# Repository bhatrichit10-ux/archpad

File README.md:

# Archpad
A custom-made macropad/hackpad for arch users. <br>Made for blueprint by Hack Club

## PCB (Printed Circuit Board)
The files of PCBs is inside the PCB folder, It contains a KiCad Project, a schematic file and a pcb file. <br>
[PCB file](PCB/richit.kicad_pcb) <br>
[Project File](PCB/richit.kicad_pro) <br>
[Schematic Files](PCB/richit.kicad_sch)
### Images:

## Case (CAD)

### Files: 
[Stp_TOP](production/Archpad_Top_latest.stp) <br>
[Stp_Bottom_Case](production/Archpad_Latest.stp)
## Firmware
The firmware is coded in ~~KMK~~ `adafruit_hid` which is in python.<br>
I have taken help of ChatGPT in this part <br>
[code.py](firmware/HID/code.py)
## Building
It took  me approx 9 hours to physically build this. Here is the final result

## BOM
- Seeed XIAO RP2040 ×1
- MX-style mechanical switches ×6
- Blank DSA keycaps (white) ×6
- 0.91 inch OLED display (SSD1306, I2C) ×1
- SK6812 MINI-E RGB LED ×1
- M3 × 16 mm screws ×4
- M3 heat-set inserts ×4
- 3D printed case ×1
## Thanks HackClub
Special thanks to HackClub and Blueprint for providing this opportunity. 
Join them : [HackClub](https://hackclub.com) <br>
Blueprint : [Blueprint](https://blueprint.hackclub.com)
## Whats next?
I am working on making another cool projects like this

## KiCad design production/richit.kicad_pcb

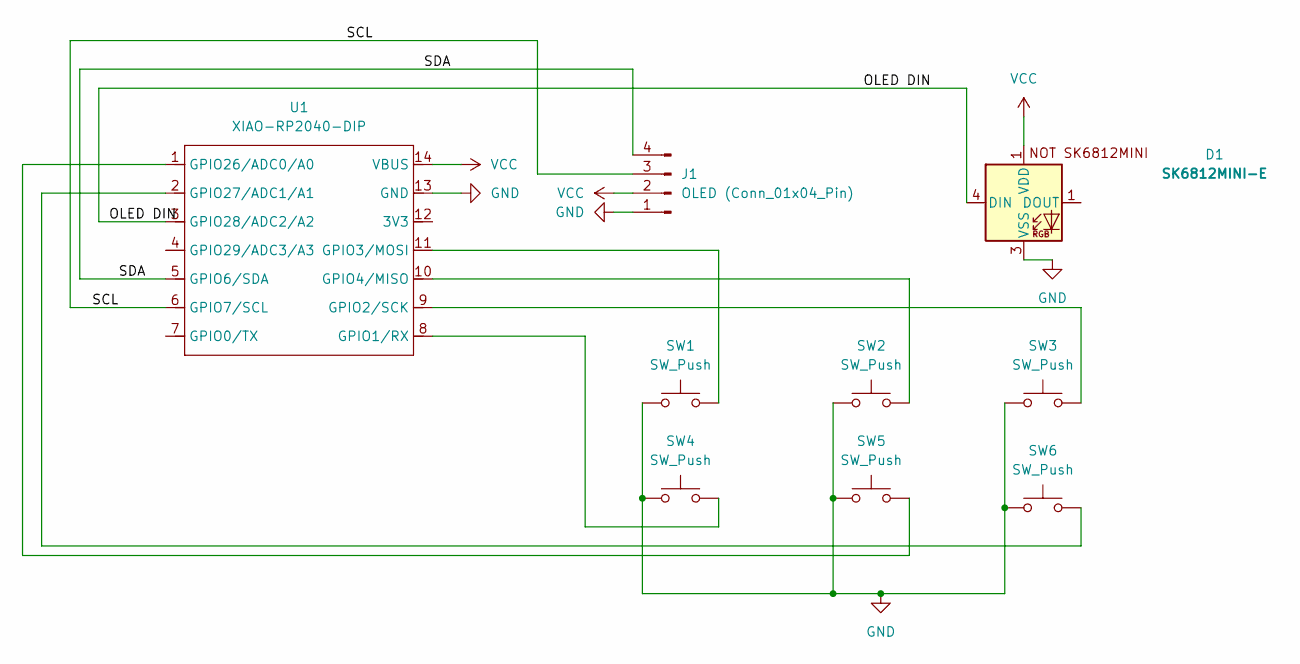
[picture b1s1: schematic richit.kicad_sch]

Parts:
D1: SK6812MINI-E; SK6812MINI-E_fixed
J1: OLED (Conn_01x04_Pin); SSD1306-0.91-OLED-4pin-128x32
SW1, SW2, SW3, SW4, SW5, SW6: SW_Push; SW_Cherry_MX_1.00u_PCB
U1: XIAO-RP2040-DIP; XIAO-Generic-Hybrid-14P-2.54-21X17.8MM

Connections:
/SCL: J1.3, U1.6 (GPIO7/SCL)
/SDA: J1.4, U1.5 (GPIO6/SDA)
GND: D1.3 (VSS), J1.1, SW1.1, SW2.1, SW3.1, SW4.1, SW5.1, SW6.1, U1.13 (GND)
unnamed: D1.4 (DIN), U1.3 (GPIO28/ADC2/A2)
unnamed: SW4.2, U1.8 (GPIO1/RX)
unnamed: SW3.2, U1.9 (GPIO2/SCK)
unnamed: SW1.2, U1.11 (GPIO3/MOSI)
unnamed: SW2.2, U1.10 (GPIO4/MISO)
unnamed: SW5.2, U1.1 (GPIO26/ADC0/A0)
unnamed: SW6.2, U1.2 (GPIO27/ADC1/A1)
VCC: D1.1 (VDD), J1.2, U1.14 (VBUS)

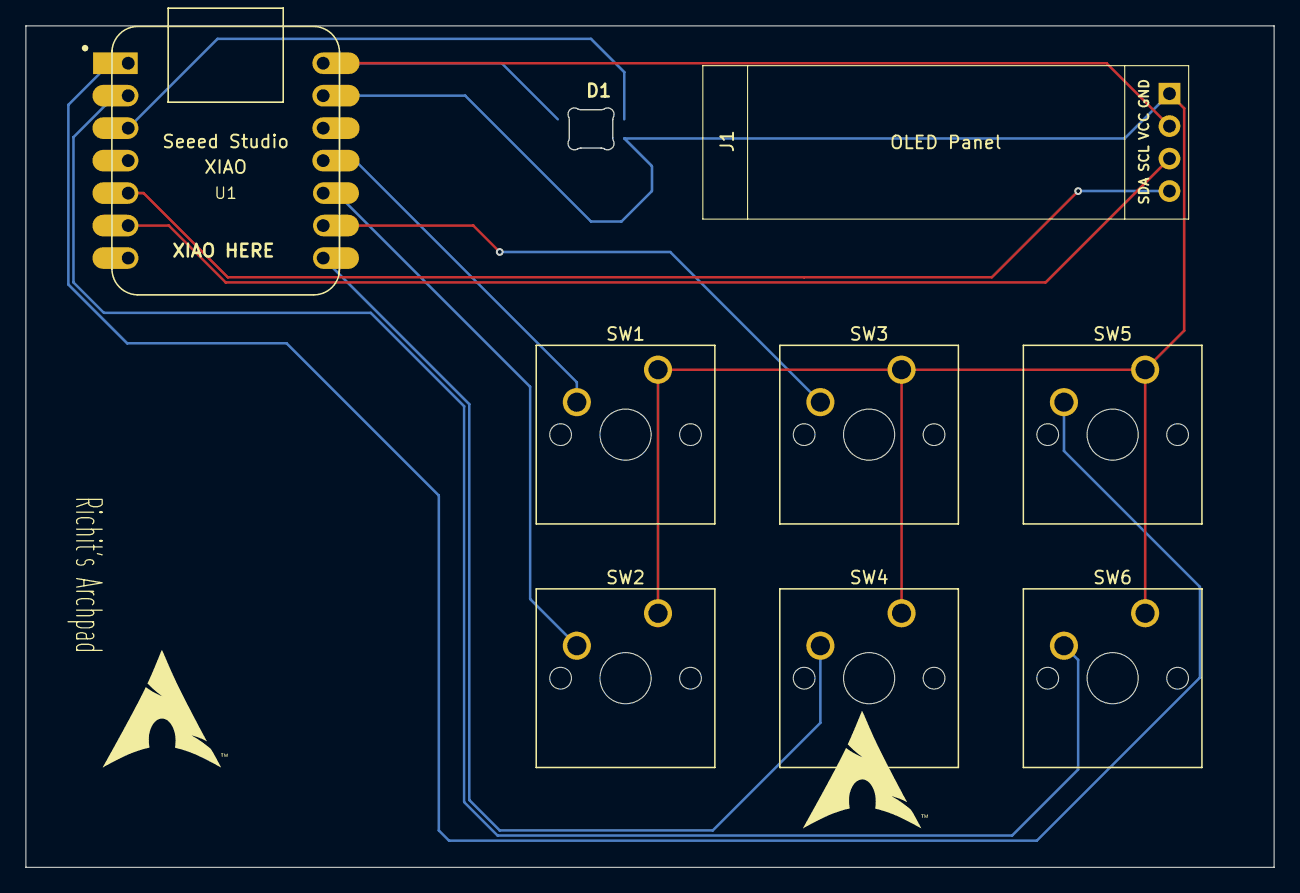
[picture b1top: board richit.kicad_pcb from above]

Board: 2 copper layers, 97.6 x 65.8 mm, 9 parts (0 on the bottom side), 11 nets.

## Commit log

2025-12-16 Added a bunch of information ;)
2025-12-16 Updated alot
2025-12-16 Updated readme bois
2025-12-16 updated alot of stuff ready for submission
2025-12-16 Ready for submission
2025-12-16 Review 2
2025-12-17 Ready for review #3
2026-01-25 Build
